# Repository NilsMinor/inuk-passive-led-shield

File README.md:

# Passive LED shield

This board is used together with the inuk base pcb. It carries five 3W white LEDs.

I just released the board to version 1.0 and it will get in production next week (20.04.2020).

###### Click on the image below to see the gerber files

##View in 3D

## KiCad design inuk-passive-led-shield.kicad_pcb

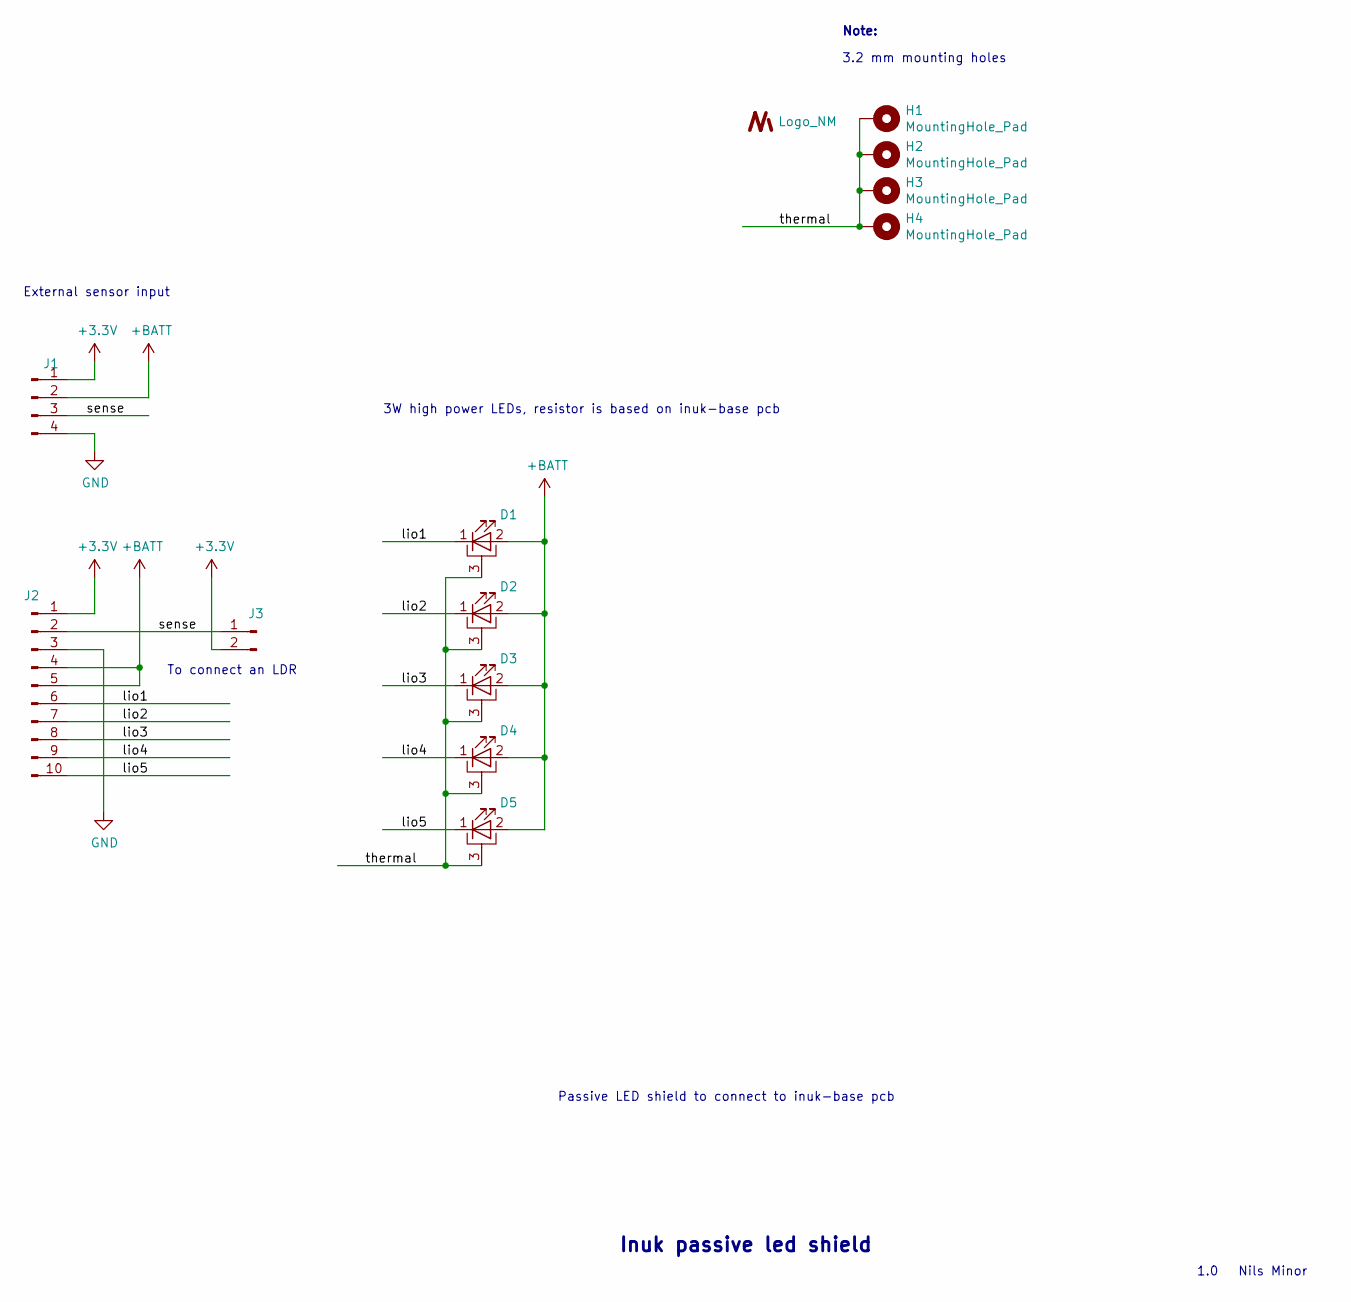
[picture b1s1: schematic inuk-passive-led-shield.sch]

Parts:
D1, D2, D3, D4, D5: LED_PAD; LED_1W_3W_R8
H1, H2, H3, H4: MountingHole_Pad; MountingHole_3.2mm_M3_Pad_Via
J1: Conn_01x04_Male; PinHeader_1x04_P2.54mm_Vertical; MPN 61300411121
J2: Conn_01x10_Male; PinHeader_1x10_P2.54mm_Horizontal; MPN 61301011121
J3: Conn_01x02_Male; PinHeader_1x02_P2.54mm_Vertical; MPN 61300211121
U1: Logo_NM

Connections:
+3V3: J1.1, J2.1, J3.2
+BATT: D1.2 (A), D2.2 (A), D3.2 (A), D4.2 (A), D5.2 (A), J1.2, J2.4, J2.5
/lio1: D1.1 (K), J2.6
/lio2: D2.1 (K), J2.7
/lio3: D3.1 (K), J2.8
/lio4: D4.1 (K), J2.9
/lio5: D5.1 (K), J2.10
/sense: J1.3, J2.2, J3.1
/thermal: D1.3 (PAD), D2.3 (PAD), D3.3 (PAD), D4.3 (PAD), D5.3 (PAD), H1.1, H2.1, H3.1, H4.1
GND: J1.4, J2.3

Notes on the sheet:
To connect an LDR
Note:
3.2 mm mounting holes
External sensor input
3W high power LEDs, resistor is based on inuk-base pcb
Inuk passive led shield
1.0
Nils Minor
Passive LED shield to connect to inuk-base pcb

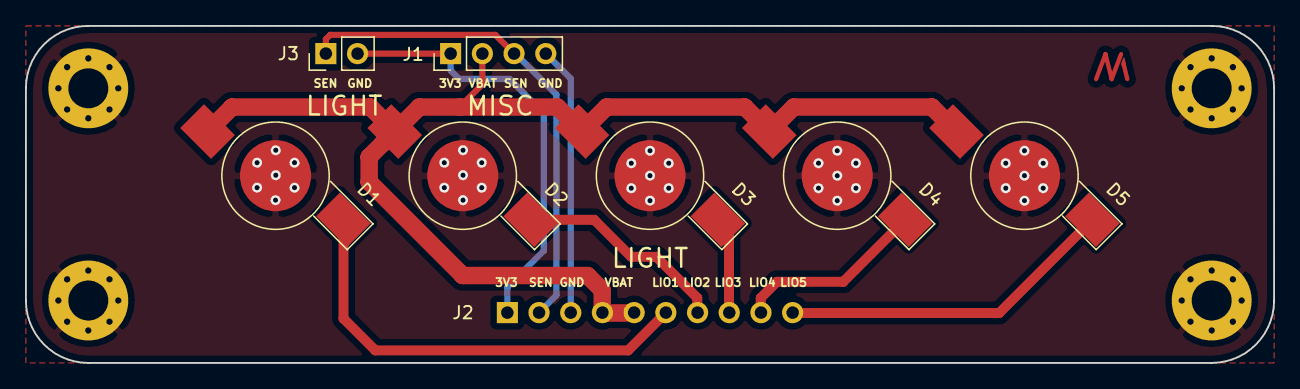
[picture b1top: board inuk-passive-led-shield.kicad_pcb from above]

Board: 2 copper layers, 100.0 x 27.0 mm, 13 parts (1 on the bottom side), 10 nets.

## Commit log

2020-04-13 added logo and info text for rev 0.9
2020-04-17 resized board to 27 x 100 to fit on 100x100 panel
2020-04-19 created production files
